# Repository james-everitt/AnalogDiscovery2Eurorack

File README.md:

# AnalogDiscovery2Eurorack
Breakout board for the Digilent Analog Discovery 2 for Eurorack module testing and calibration

SSW-115-02-G-D-RA header just fits into the Analog Discovery 2, mine was a tight fit

Voltage rails and Digital I/O pins are passed through to the far header

# Crosstalk measurements
Initally I thought my breakout had bad high frequency performance; using the AD Bode plot function I measured crosstalk at ~-48dB from 5kHz upward. However doing the same measurement with the BNC adaptor board that Digilent offer, I measured -38dB of crosstalk in this same region! Make sense as I used a ground flood fill wherever possible, and the BNC board from digilent doesnt.

Eurorack adaptor crosstalk
<br>

Official BNC adaptor crosstalk

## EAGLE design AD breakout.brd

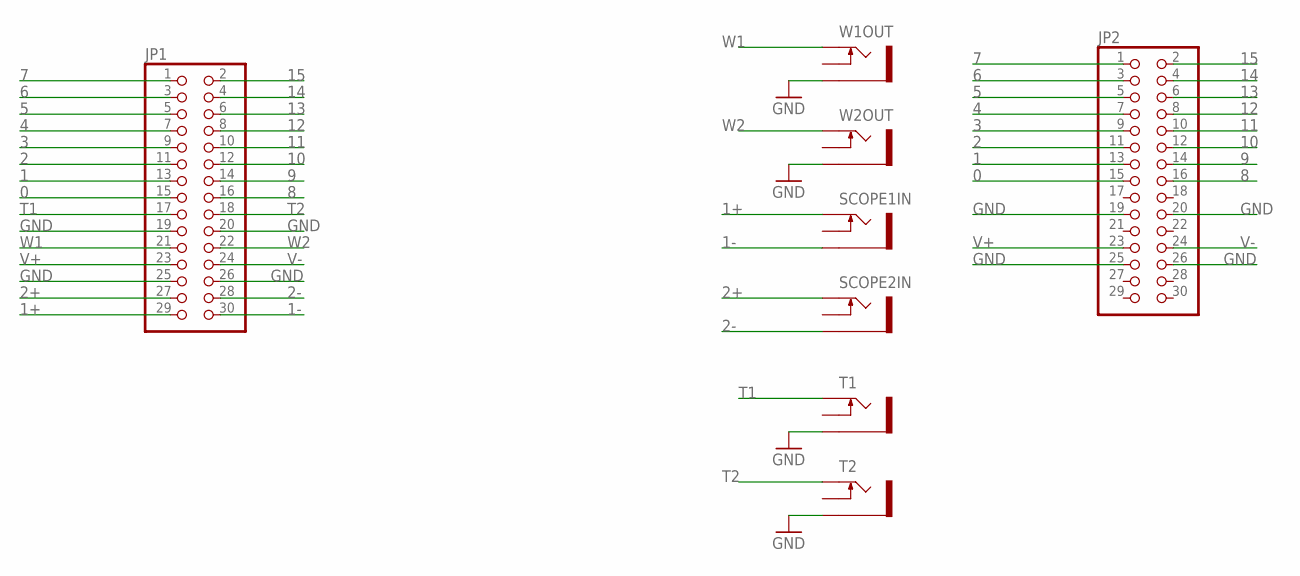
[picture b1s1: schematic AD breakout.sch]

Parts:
JP1, JP2: PINHD-2X15; 2X15
SCOPE1IN, SCOPE2IN: THONKICONNNEW; WQP-PJ301M-12_JACK
T1, T2: THONKICONNNEW; WQP-PJ301M-12_JACK
W1OUT, W2OUT: THONKICONNNEW; WQP-PJ301M-12_JACK

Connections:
0: JP1.15, JP2.15
1: JP1.13, JP2.13
1+: JP1.29, SCOPE1IN.P$1_TIP (TIP)
1-: JP1.30, SCOPE1IN.P$3_SLEEVE (SLEEVE)
2: JP1.11, JP2.11
2+: JP1.27, SCOPE2IN.P$1_TIP (TIP)
2-: JP1.28, SCOPE2IN.P$3_SLEEVE (SLEEVE)
3: JP1.9, JP2.9
4: JP1.7, JP2.7
5: JP1.5, JP2.5
6: JP1.3, JP2.3
7: JP1.1, JP2.1
8: JP1.16, JP2.16
9: JP1.14, JP2.14
10: JP1.12, JP2.12
11: JP1.10, JP2.10
12: JP1.8, JP2.8
13: JP1.6, JP2.6
14: JP1.4, JP2.4
15: JP1.2, JP2.2
GND: JP1.19, JP1.20, JP1.25, JP1.26, JP2.19, JP2.20, JP2.25, JP2.26, T1.P$3_SLEEVE (SLEEVE), T2.P$3_SLEEVE (SLEEVE), W1OUT.P$3_SLEEVE (SLEEVE), W2OUT.P$3_SLEEVE (SLEEVE)
T1: JP1.17, T1.P$1_TIP (TIP)
T2: JP1.18, T2.P$1_TIP (TIP)
V+: JP1.23, JP2.23
V-: JP1.24, JP2.24
W1: JP1.21, W1OUT.P$1_TIP (TIP)
W2: JP1.22, W2OUT.P$1_TIP (TIP)

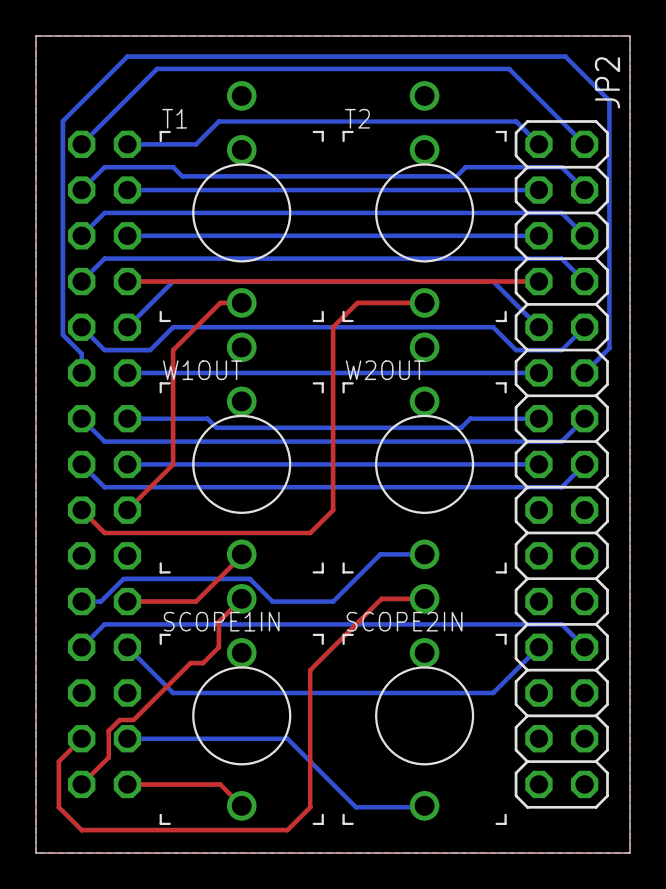
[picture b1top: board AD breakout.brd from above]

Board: 2 copper layers, 33.0 x 45.4 mm, 8 parts (1 on the bottom side), 27 nets.

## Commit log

2019-01-02 Add files via upload
    Crosstalk measurements
